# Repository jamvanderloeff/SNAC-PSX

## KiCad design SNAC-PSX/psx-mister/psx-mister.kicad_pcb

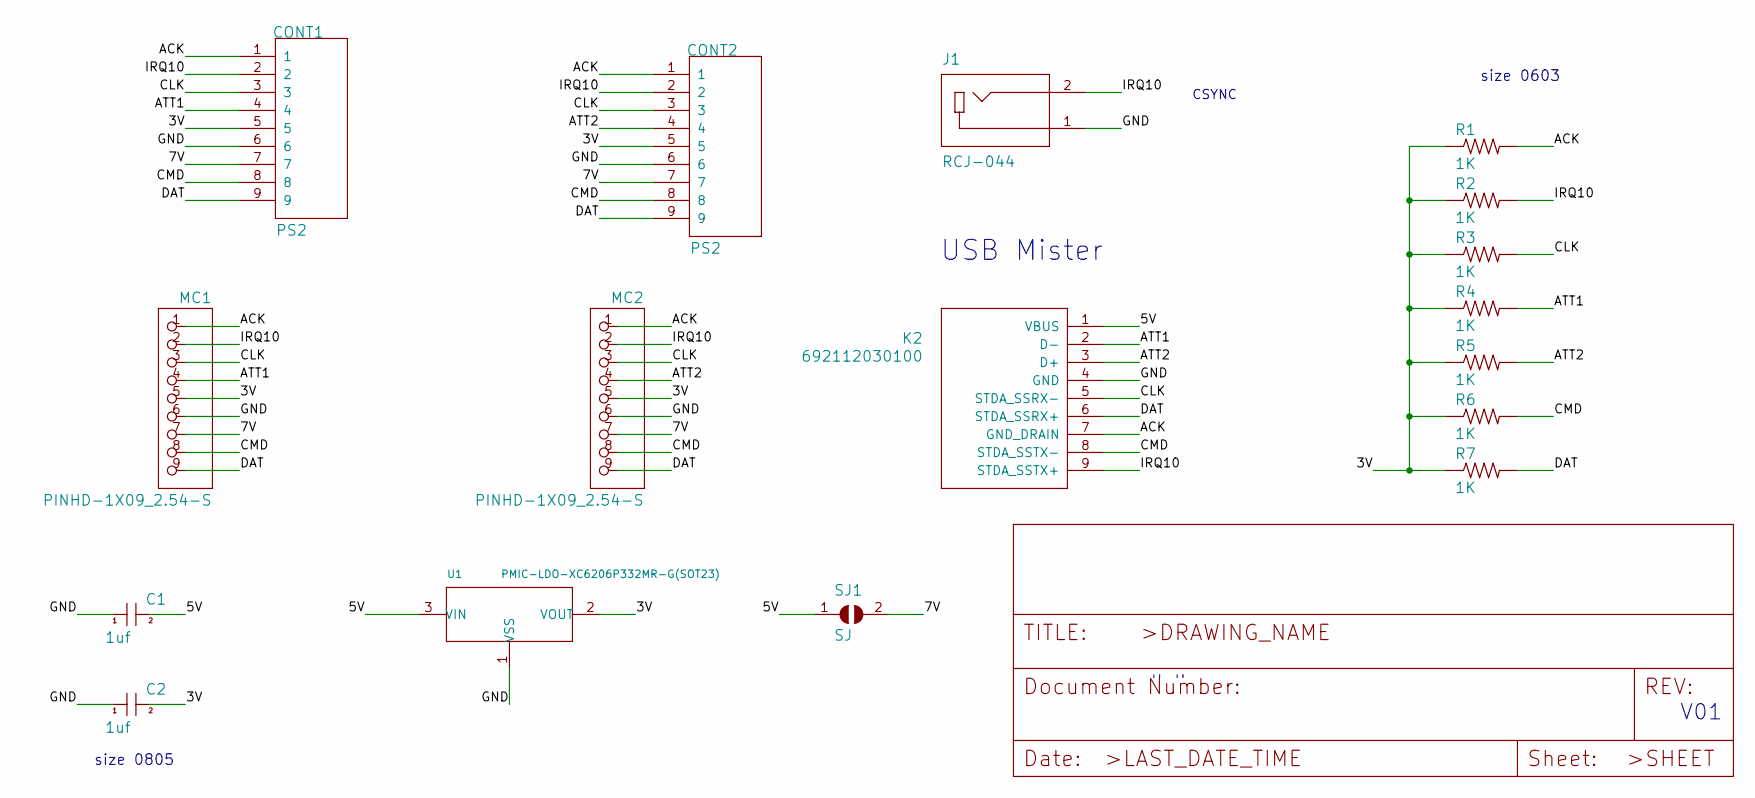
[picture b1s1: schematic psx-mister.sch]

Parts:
C1, C2: 1uf; C0805
CONT1, CONT2: PS2; TE_PS2
J1: RCJ-044; CUI_RCJ-044
K2: 692112030100
MC1, MC2: PINHD-1X09_2.54-S; 1X09-S
R1, R2, R3, R4, R5, R6, R7: 1K; 0603-RES
SJ1: SJ
U1: PMIC-LDO-XC6206P332MR-G(SOT23); SOT-23

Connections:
/3V: C2.2, CONT1.5, CONT2.5, MC1.5, MC2.5, R1.1, R2.1, R3.1, R4.1, R5.1, R6.1, R7.1, U1.2 (VOUT)
/5V: C1.2, K2.1 (VBUS), SJ1.1, U1.3 (VIN)
/7V: CONT1.7, CONT2.7, MC1.7, MC2.7, SJ1.2
/ACK: CONT1.1, CONT2.1, K2.7 (GND_DRAIN), MC1.1, MC2.1, R1.2
/ATT1: CONT1.4, K2.2 (D-), MC1.4, R4.2
/ATT2: CONT2.4, K2.3 (D+), MC2.4, R5.2
/CLK: CONT1.3, CONT2.3, K2.5 (STDA_SSRX-), MC1.3, MC2.3, R3.2
/CMD: CONT1.8, CONT2.8, K2.8 (STDA_SSTX-), MC1.8, MC2.8, R6.2
/DAT: CONT1.9, CONT2.9, K2.6 (STDA_SSRX+), MC1.9, MC2.9, R7.2
/GND: C1.1, C2.1, CONT1.6, CONT2.6, J1.1, K2.4 (GND), MC1.6, MC2.6, U1.1 (VSS)
/IRQ10: CONT1.2, CONT2.2, J1.2, K2.9 (STDA_SSTX+), MC1.2, MC2.2, R2.2

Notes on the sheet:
V01
" "
USB Mister
size 0805
CSYNC
size 0603

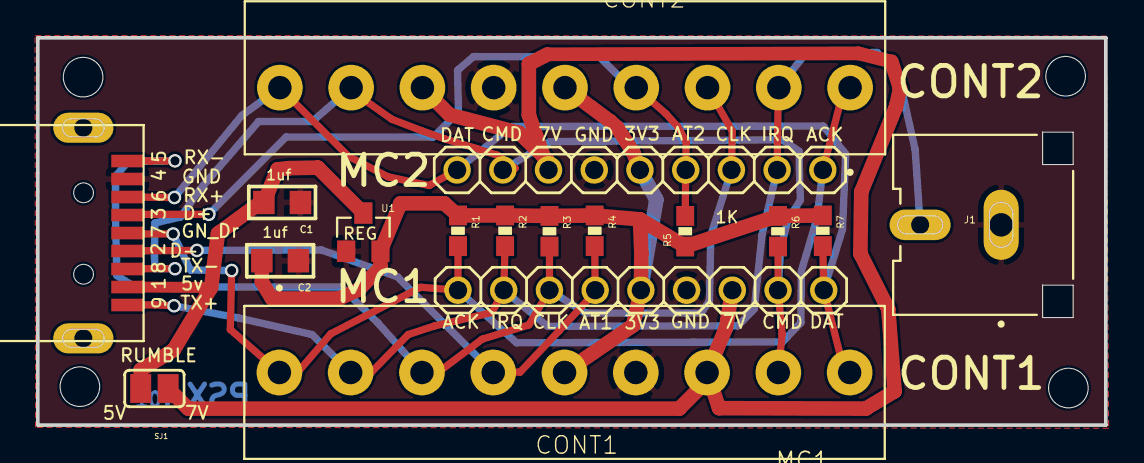
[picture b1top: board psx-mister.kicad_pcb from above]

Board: 2 copper layers, 59.3 x 21.5 mm, 23 parts (0 on the bottom side), 11 nets.

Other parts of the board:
@HOLE0, @HOLE1, @HOLE2, @HOLE3, @HOLE4, @HOLE5: (no value)

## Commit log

2022-05-25 KiCAD 6 conversion
